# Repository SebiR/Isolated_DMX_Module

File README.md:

# Isolated DMX module
A module that can be used to create an isolated DMX or RS485 input and output for your project

## Features
* For 3.3V and 5V systems
* Isolated up to 1kV
* protection on isolated side
* Comes with a small eval board

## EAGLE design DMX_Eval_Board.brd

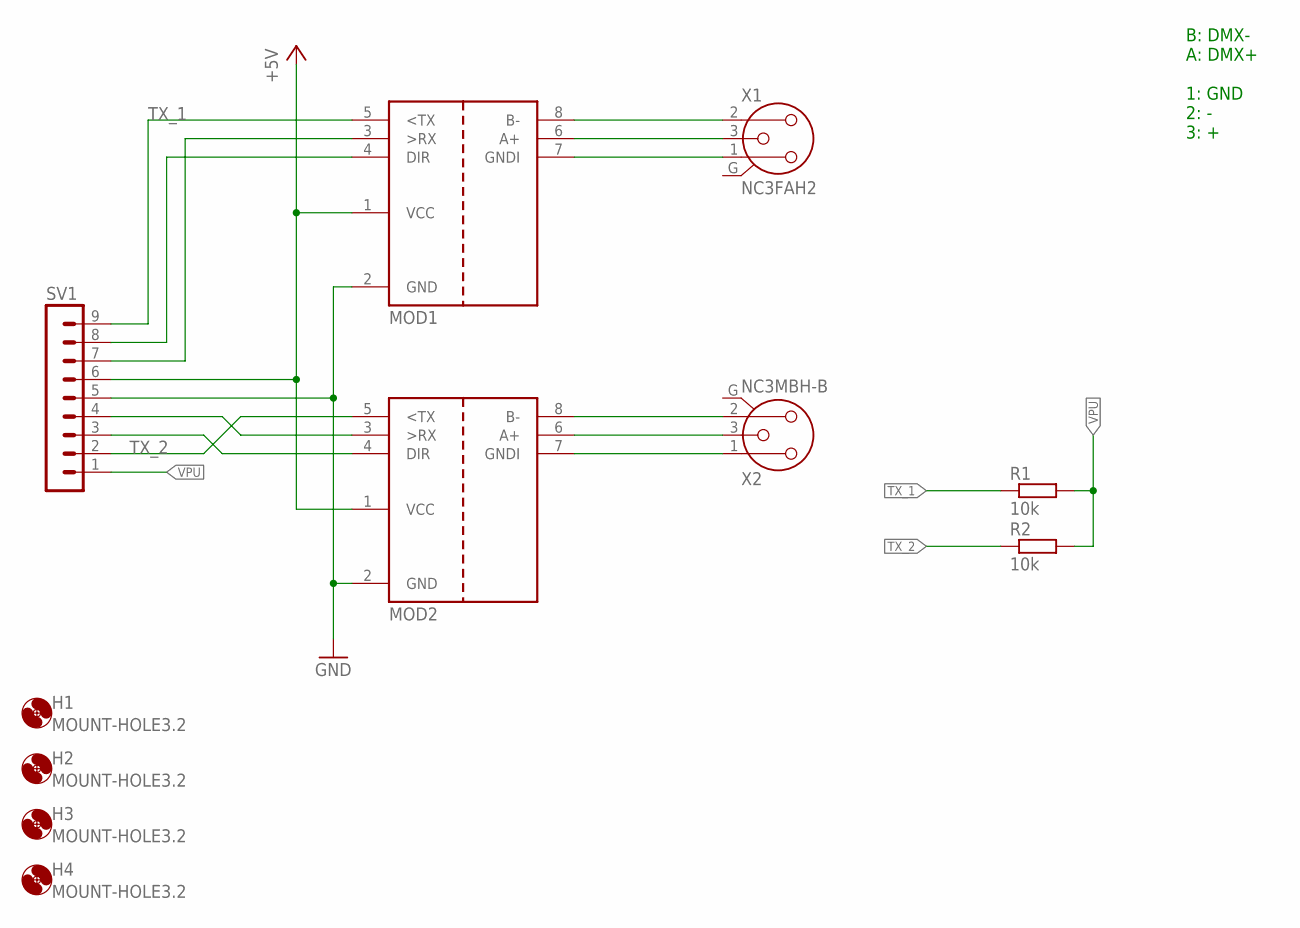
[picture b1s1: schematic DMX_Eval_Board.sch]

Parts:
H1, H2, H3, H4: MOUNT-HOLE3.2; 3,2
MOD1, MOD2: ISOL_DMX_TRANSCEIVER; MODULE_DMX_ISO
R1, R2: 10k; R0603
SV1: MA09-1
X1: NC3FAH2
X2: NC3MBH-B

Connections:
+5V: MOD1.1 (VCC), MOD2.1 (VCC), SV1.6
GND: MOD1.2 (GND), MOD2.2 (GND), SV1.5
unnamed: MOD1.7 (GNDI), X1.1 (2)
unnamed: MOD2.7 (GNDI), X2.1
unnamed: MOD2.8 (B-), X2.2
unnamed: MOD2.6 (A+), X2.3
unnamed: MOD1.6 (A+), X1.3
unnamed: MOD1.8 (B-), X1.2 (1)
unnamed: MOD2.4 (DIR), SV1.3
unnamed: MOD2.3 (>RX), SV1.4
unnamed: MOD1.4 (DIR), SV1.8
unnamed: MOD1.3 (>RX), SV1.7
TX_1: MOD1.5 (<TX), R1.1, SV1.9
TX_2: MOD2.5 (<TX), R2.1, SV1.2
VPU: R1.2, R2.2, SV1.1

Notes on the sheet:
B: DMX- A: DMX+ 1: GND 2: - 3: +

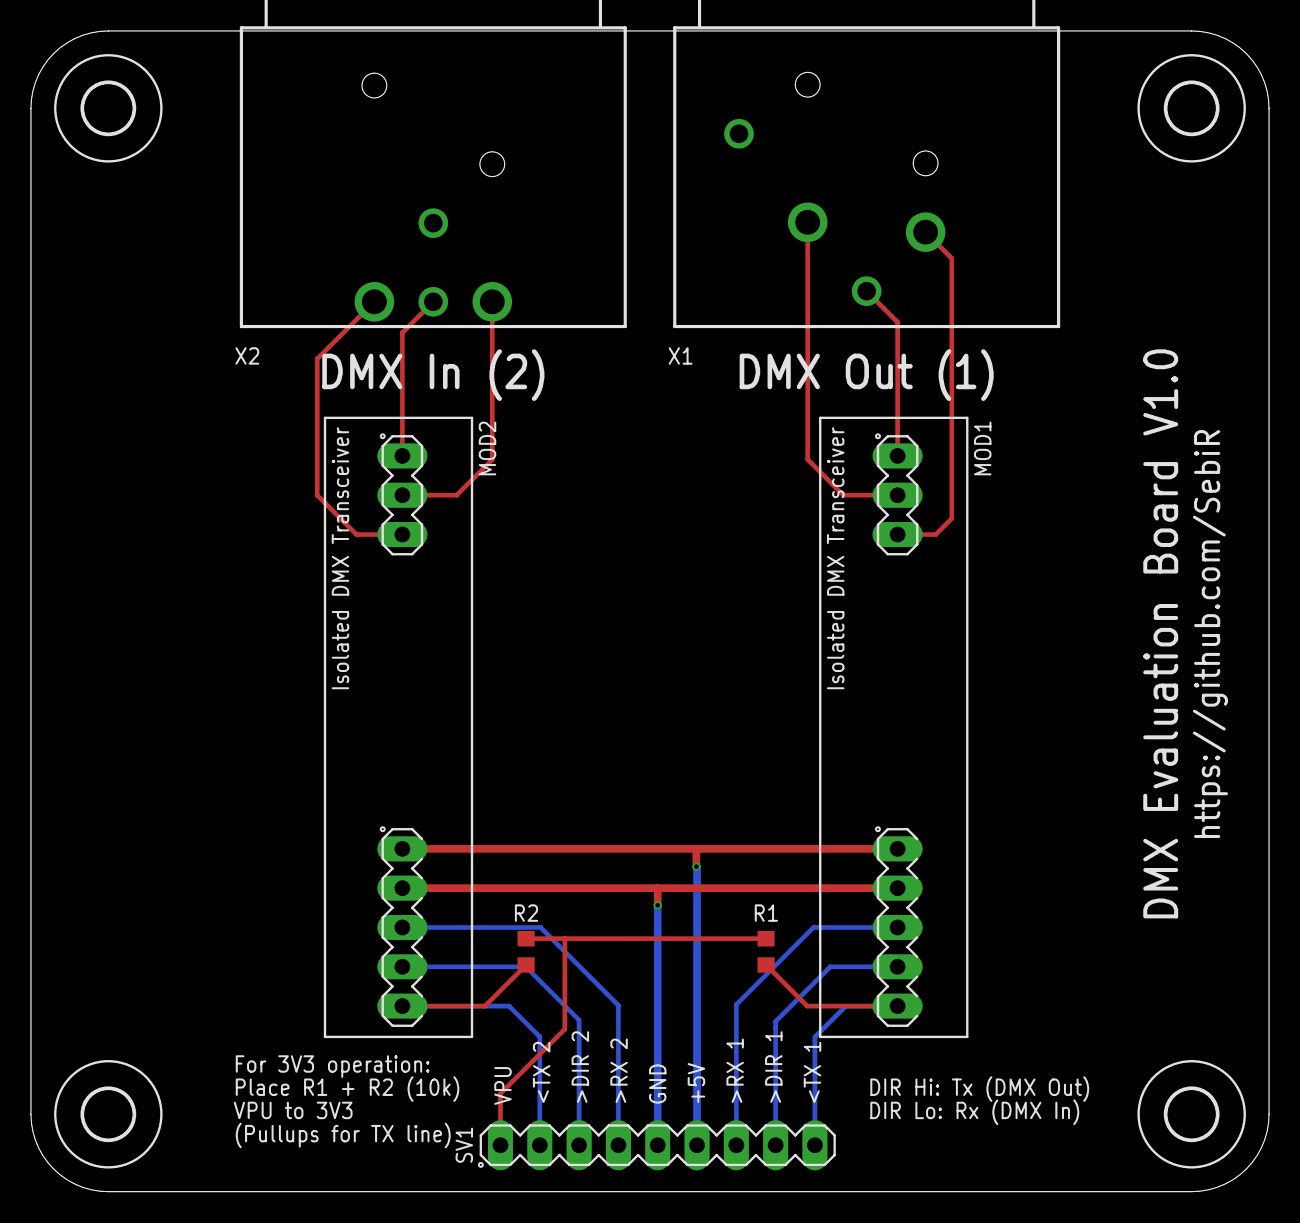
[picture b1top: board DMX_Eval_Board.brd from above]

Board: 2 copper layers, 80.0 x 75.0 mm, 11 parts (0 on the bottom side), 15 nets.

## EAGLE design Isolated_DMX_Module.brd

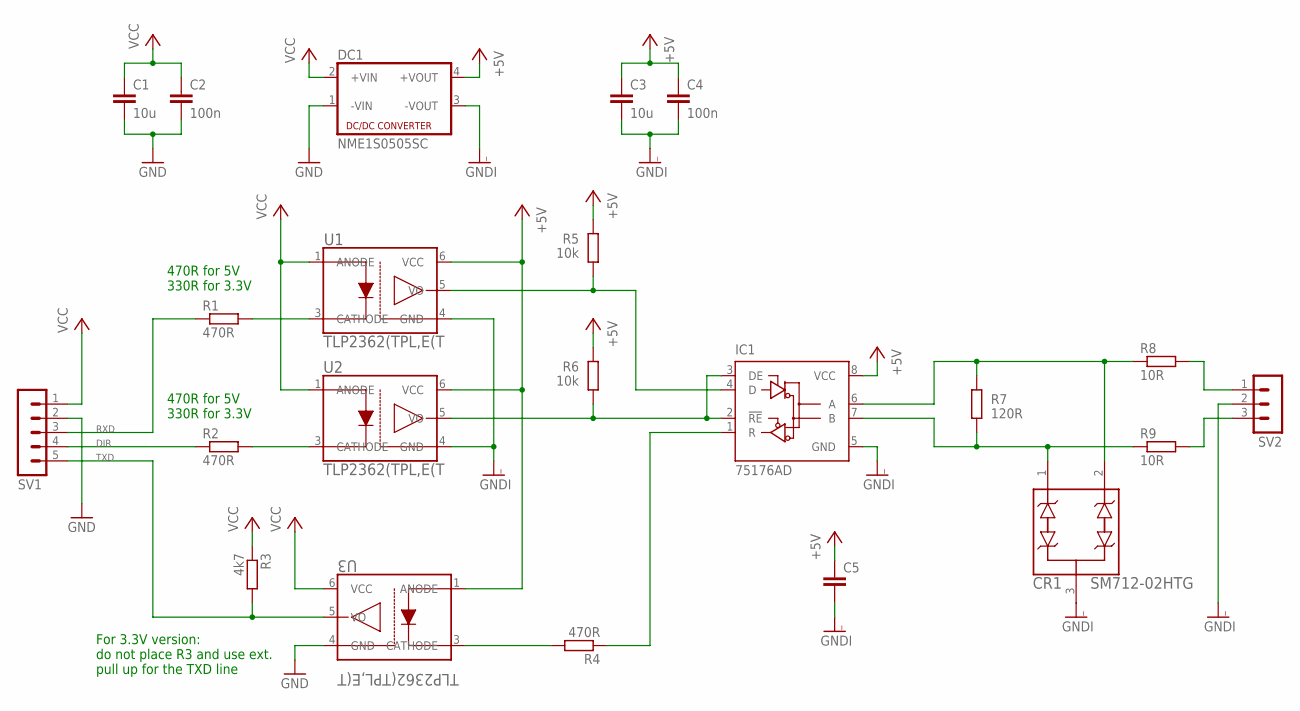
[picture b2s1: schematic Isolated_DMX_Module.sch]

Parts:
C1, C3: 10u; C0805
C2, C4: 100n; C0603
C5: C-EUC0603; C0603
CR1: SM712-02HTG; SOT23-3_LTF
DC1: NME1S0505SC; NME_FLAT
IC1: 75176AD; D_R-PDSO-G8
R1, R2, R4: 470R; R0603
R3: 4k7; R0603
R5, R6: 10k; R0603
R7: 120R; R0603
R8, R9: 10R; R0603
SV1: MA05-1
SV2: MA03-1
U1, U2, U3: TLP2362(TPL,E(T; 11-4L1S_TOS

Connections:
+5V: C3.1, C4.1, C5.1, DC1.4 (+VOUT), IC1.8 (VCC), R5.1, R6.1, U1.6 (VCC), U2.6 (VCC), U3.1 (ANODE)
DIR: R2.1, SV1.4
GND: C1.2, C2.2, DC1.1 (-VIN), SV1.2, U3.4 (GND)
GNDI: C3.2, C4.2, C5.2, CR1.3, DC1.3 (-VOUT), IC1.5 (GND), SV2.2, U1.4 (GND), U2.4 (GND)
unnamed: IC1.1 (R), R4.1
unnamed: R4.2, U3.3 (CATHODE)
unnamed: IC1.2 (!RE), IC1.3 (DE), R6.2, U2.5 (VO)
unnamed: IC1.4 (D), R5.2, U1.5 (VO)
unnamed: R1.2, U1.3 (CATHODE)
unnamed: R2.2, U2.3 (CATHODE)
unnamed: R8.2, SV2.1
unnamed: R9.2, SV2.3
unnamed: CR1.2, IC1.6 (A), R7.1, R8.1
unnamed: CR1.1, IC1.7 (B), R7.2, R9.1
RXD: R1.1, SV1.3
TXD: R3.2, SV1.5, U3.5 (VO)
VCC: C1.1, C2.1, DC1.2 (+VIN), R3.1, SV1.1, U1.1 (ANODE), U2.1 (ANODE), U3.6 (VCC)

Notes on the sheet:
470R for 5V 330R for 3.3V
For 3.3V version: do not place R3 and use ext. pull up for the TXD line

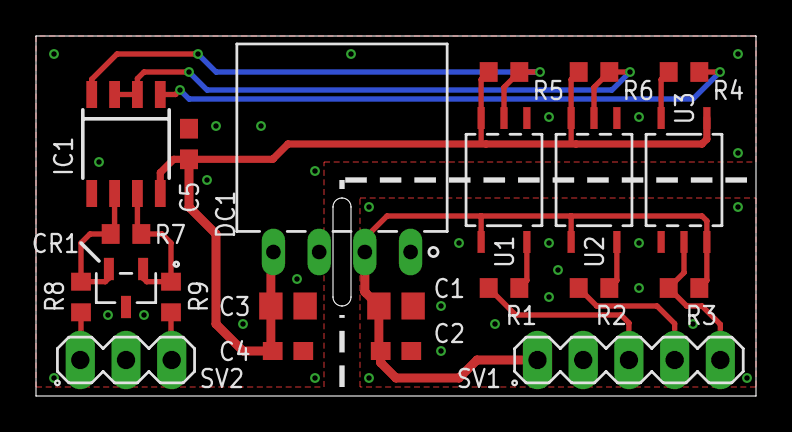
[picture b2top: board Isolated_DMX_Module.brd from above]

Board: 2 copper layers, 40.0 x 20.0 mm, 22 parts (0 on the bottom side), 17 nets.

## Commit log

2025-06-01 fixed image link
2025-06-01 updated readme to include features
2025-06-04 Updated spacing between pin headers to be within a 0.1" grid - This way it is breadboard compatible

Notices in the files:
parts and their libraries:
COPYRIGHT: Copyright (C) 2024 Ultra Librarian. All rights reserved.
